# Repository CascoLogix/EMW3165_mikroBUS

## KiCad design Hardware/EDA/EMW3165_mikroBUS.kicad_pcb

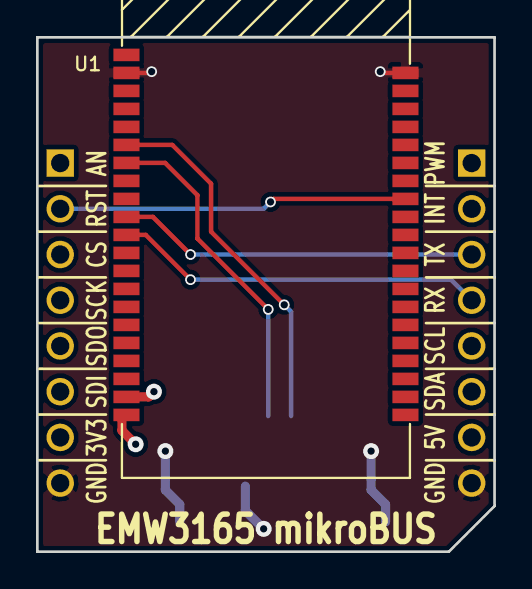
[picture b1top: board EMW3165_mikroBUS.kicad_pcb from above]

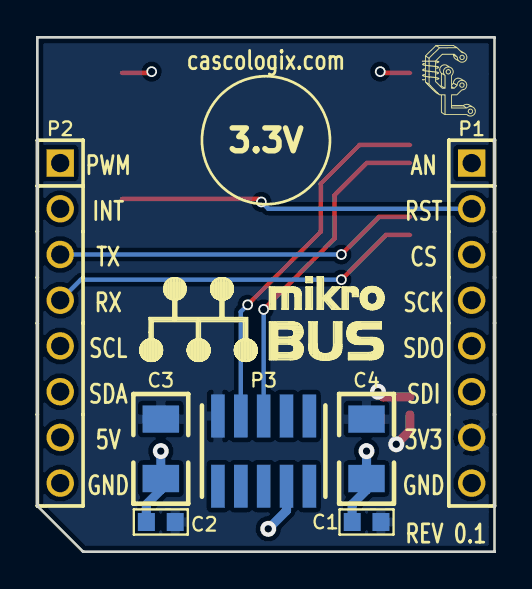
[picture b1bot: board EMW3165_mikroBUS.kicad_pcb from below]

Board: 2 copper layers, 25.4 x 28.6 mm, 9 parts (8 on the bottom side), 7 nets.

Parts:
C1: 0.1uF; 0603
C2: 1uF; 0603
C3, C4: 47uF; 1206
G1: LOGO; Casco_Logix_Logo_4x4MM
P1, P2: HEADER_M_2.54MM_1R8P_ST_AU_PTH
P3: JTAG; HEADER_M_1.27MM_2R10P_ST_AU_SMT
U1: EMW3165; EMW3165_SMT

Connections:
+3.3V: C1.1, C2.1, C3.1, C4.1, P1.7, P3.2, U1.39, U1.40
GND: C1.2, C2.2, C3.2, C4.2, P1.8, P2.8, P3.7, U1.20, U1.21
JTCK/SWCLK: P3.4, U1.25
JTMS/SWDIO: P3.6, U1.26
RST: P1.2, U1.13
USART1_RX: P2.3, U1.29
USART1_TX: P2.4, U1.30

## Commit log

2016-12-11 First commit.
2016-12-11 Final prototype layout. Ordered from OSH Park.
